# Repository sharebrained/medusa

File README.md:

Medusa
======

Gonzo LED strip lighting controller, driven from video output that's easy to program.

The hardware is in three parts:

* Medusa Cape: BeagleBone Black cape that snoops the LCD video output of the BeagleBone and picks off RGB pixel values. Those values are mapped to LED pixels on one of 32 WS2811/WS2812 LED strips of up to 512 LEDs each.
* Medusa TX32: A 32-channel RS-422 transmitter board that sends 4 pairs of RS-422 signalling out of each of eight RJ-45 connectors. Common CAT5/6 Ethernet cabling (TIA-568B) can be used to connect up to four strips on each cable.
* Medusa RX2: A 2-channel RS-422 receiver board that picks off two channels of RS-422 on a cable, and passes the two remaining signals out another cable (so two 2-channel receivers can be chained to use all four channels on a single Ethernet cable).

Dependencies
============

For developing this project, the following tools were used:

* Schematic capture and PCB layout: KiCAD -testing branch, builds from late September or early October 2013
* FPGA development and bitstream generation: Altera Quartus II 13.0 SP 1 FPGA development environment, for Windows or Linux
* BeagleBone Linux distribution: Angstrom, September 4, 2013
* Python 2.7

License
=======

The associated software is provided under a GPLv2 license:

Copyright (C) 2013 Jared Boone, ShareBrained Technology, Inc.

This program is free software; you can redistribute it and/or
modify it under the terms of the GNU General Public License
as published by the Free Software Foundation; either version 2
of the License, or (at your option) any later version.

This program is distributed in the hope that it will be useful,
but WITHOUT ANY WARRANTY; without even the implied warranty of
MERCHANTABILITY or FITNESS FOR A PARTICULAR PURPOSE.  See the
GNU General Public License for more details.

You should have received a copy of the GNU General Public License
along with this program; if not, write to the Free Software
Foundation, Inc., 51 Franklin Street, Fifth Floor, Boston, MA
02110-1301, USA.

Contact
=======

Jared Boone <jared@sharebrained.com>

ShareBrained Technology, Inc.

<http://www.sharebrained.com/>

The latest version of this repository can be found at
https://github.com/sharebrained/medusa

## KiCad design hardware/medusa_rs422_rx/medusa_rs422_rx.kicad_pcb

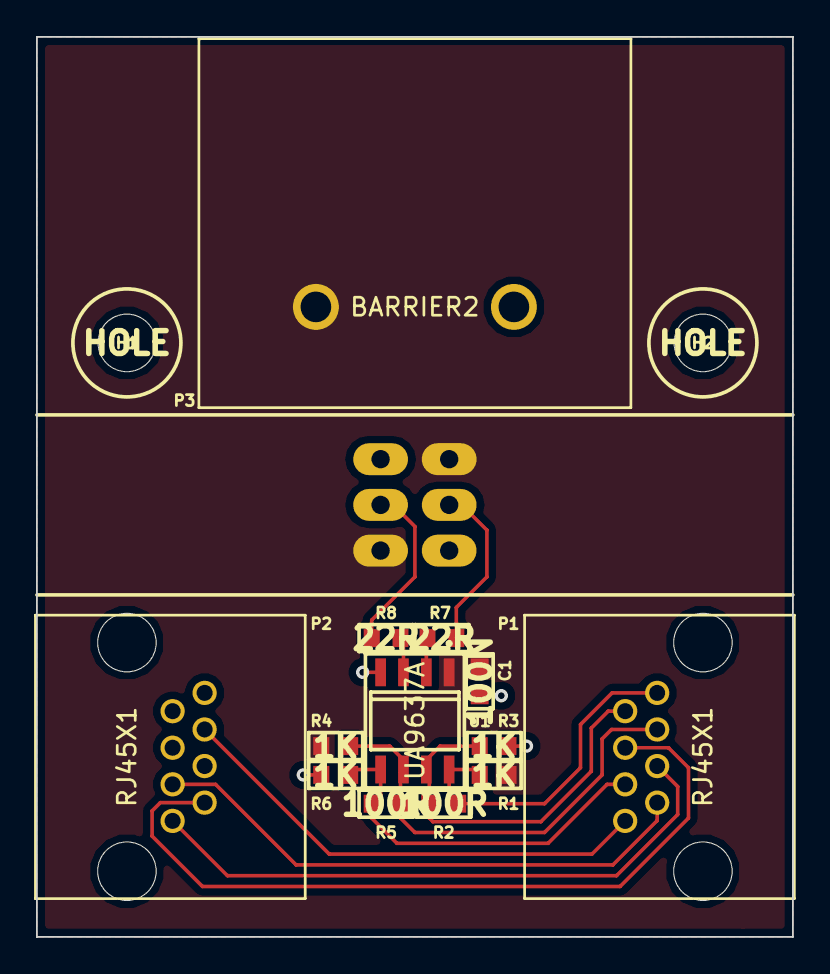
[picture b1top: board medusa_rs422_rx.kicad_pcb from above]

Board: 2 copper layers, 42.0 x 50.0 mm, 16 parts (1 on the bottom side), 14 nets.

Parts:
C1: 100N; IPC_CAPC1608X95N
H1, H2: HOLE; HOLE_3P2MM
J1: HEADER_2X3; LED_STRIP_WS2812
P1, P2: RJ45X1; AMPHENOL_RJHSE5080
P3: BARRIER2; ONSHORE_OSTYK55102030
R1, R3, R4, R6: 1K; IPC_RESC1608X55N
R2, R5: 100R; IPC_RESC1608X55N
R7, R8: 22R; IPC_RESC1608X55N
U1: UA9637A; IPC_SOIC127P600X175-8N

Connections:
+5V: C1.1, J1.1, J1.6, P3.1, R1.2, R4.2, U1.1
/DI_A: J1.3, R8.2
/DI_B: J1.4, R7.2
/PT1N: P1.4, P2.2
/PT1P: P1.5, P2.1
/PT2N: P1.8, P2.6
/PT2P: P1.7, P2.3
/RX1N: P1.2, R2.1, R3.2, U1.7
/RX1P: P1.1, R1.1, R2.2, U1.8
/RX2N: P1.6, R5.1, R6.2, U1.5
/RX2P: P1.3, R4.1, R5.2, U1.6
GND: C1.2, J1.2, J1.5, P3.2, R3.1, R6.1, U1.4
Net-<R7-Pad1>: R7.1, U1.2
Net-<R8-Pad1>: R8.1, U1.3

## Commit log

2013-11-02 Initial release of Medusa hardware (BeagleBone cape, TX32, RX2) and HDL code.
2013-11-02 Fleshed out README.md a bit. License, dependencies, hardware description.
2013-11-02 Images of Medusa Cape and Ada's Technical Books installation.
2013-11-02 Added images to README.md.
2013-12-05 Remove comma in Verilog that makes ModelSim angry.
2013-12-05 Parameterize WS2812 signal durations.
2013-12-05 Factor out the RAM block from the WS2812 protocol module.
2013-12-05 Refactor pixel RAM to implement only what's necessary (no read of port A, no write of port B).
2013-12-05 Ignored files cluttering up my repo.
2013-12-05 Revise ws2812 module to use module parameter syntax.
2013-12-05 Rename some ws2812 signals to make them shorter but clearer.
2013-12-05 Extract signal led_pixel_count_advance.
2013-12-05 Extract led_pixel_count_init value and use it at reset to address first-pass strip readout bug, where 512 pixels are transmitted before settling into the proper LED strip length cadence.
2013-12-05 Renamed led_pixel_last to be more descriptive "led_pixel_count_last".
2013-12-05 Fix bug where last pixel in strip was not being read out.
2013-12-05 Refactor signals of led_symbol_count*, and rename an ambiguous signal.
2013-12-06 Rewrite of ws2812 module to address pipelining issues. Implementation is now not particularly pipelined, but a lot easier to follow...
2013-12-06 Quartus II .qsf project file automatically updated by version 13.1, with a bunch of stuff randomly moved around.
2013-12-06 Super-basic ws2812 testbench for observing behavior in the simulator.
2013-12-06 Add 24-bit color support, parameter for selection.
2013-12-06 Remove dead comments and code.
2013-12-06 Nail down unused strip outputs.
2013-12-06 Clean up sensitivity list warnings.
2013-12-16 Change default color mode to RGB888. It should do no harm when used with an RGB565 output.
2015-09-14 Complete rebake of RX board.
    Added ground isolation.
    Changed receiver IC to better match transmitter specs.
    Added somewhat sketchy termination + ground reference mechanism.
    Removed RJ45 connectors and passthrough in favor of a single board with four channels and terminal blocks.
    Added separate terminal blocks for power supply (+5V) and isolated power connections. If we run dedicated ground reference wires from the transmitters, this is where they'll connect.
    Added optional power regulator for 3.3V operation, if we want to experiment with MCUs at the receivers.
2015-10-11 Un-cross strip output 16 and 17.
    Wall wiring was redone, and this eccentricity was eliminated in the process.
